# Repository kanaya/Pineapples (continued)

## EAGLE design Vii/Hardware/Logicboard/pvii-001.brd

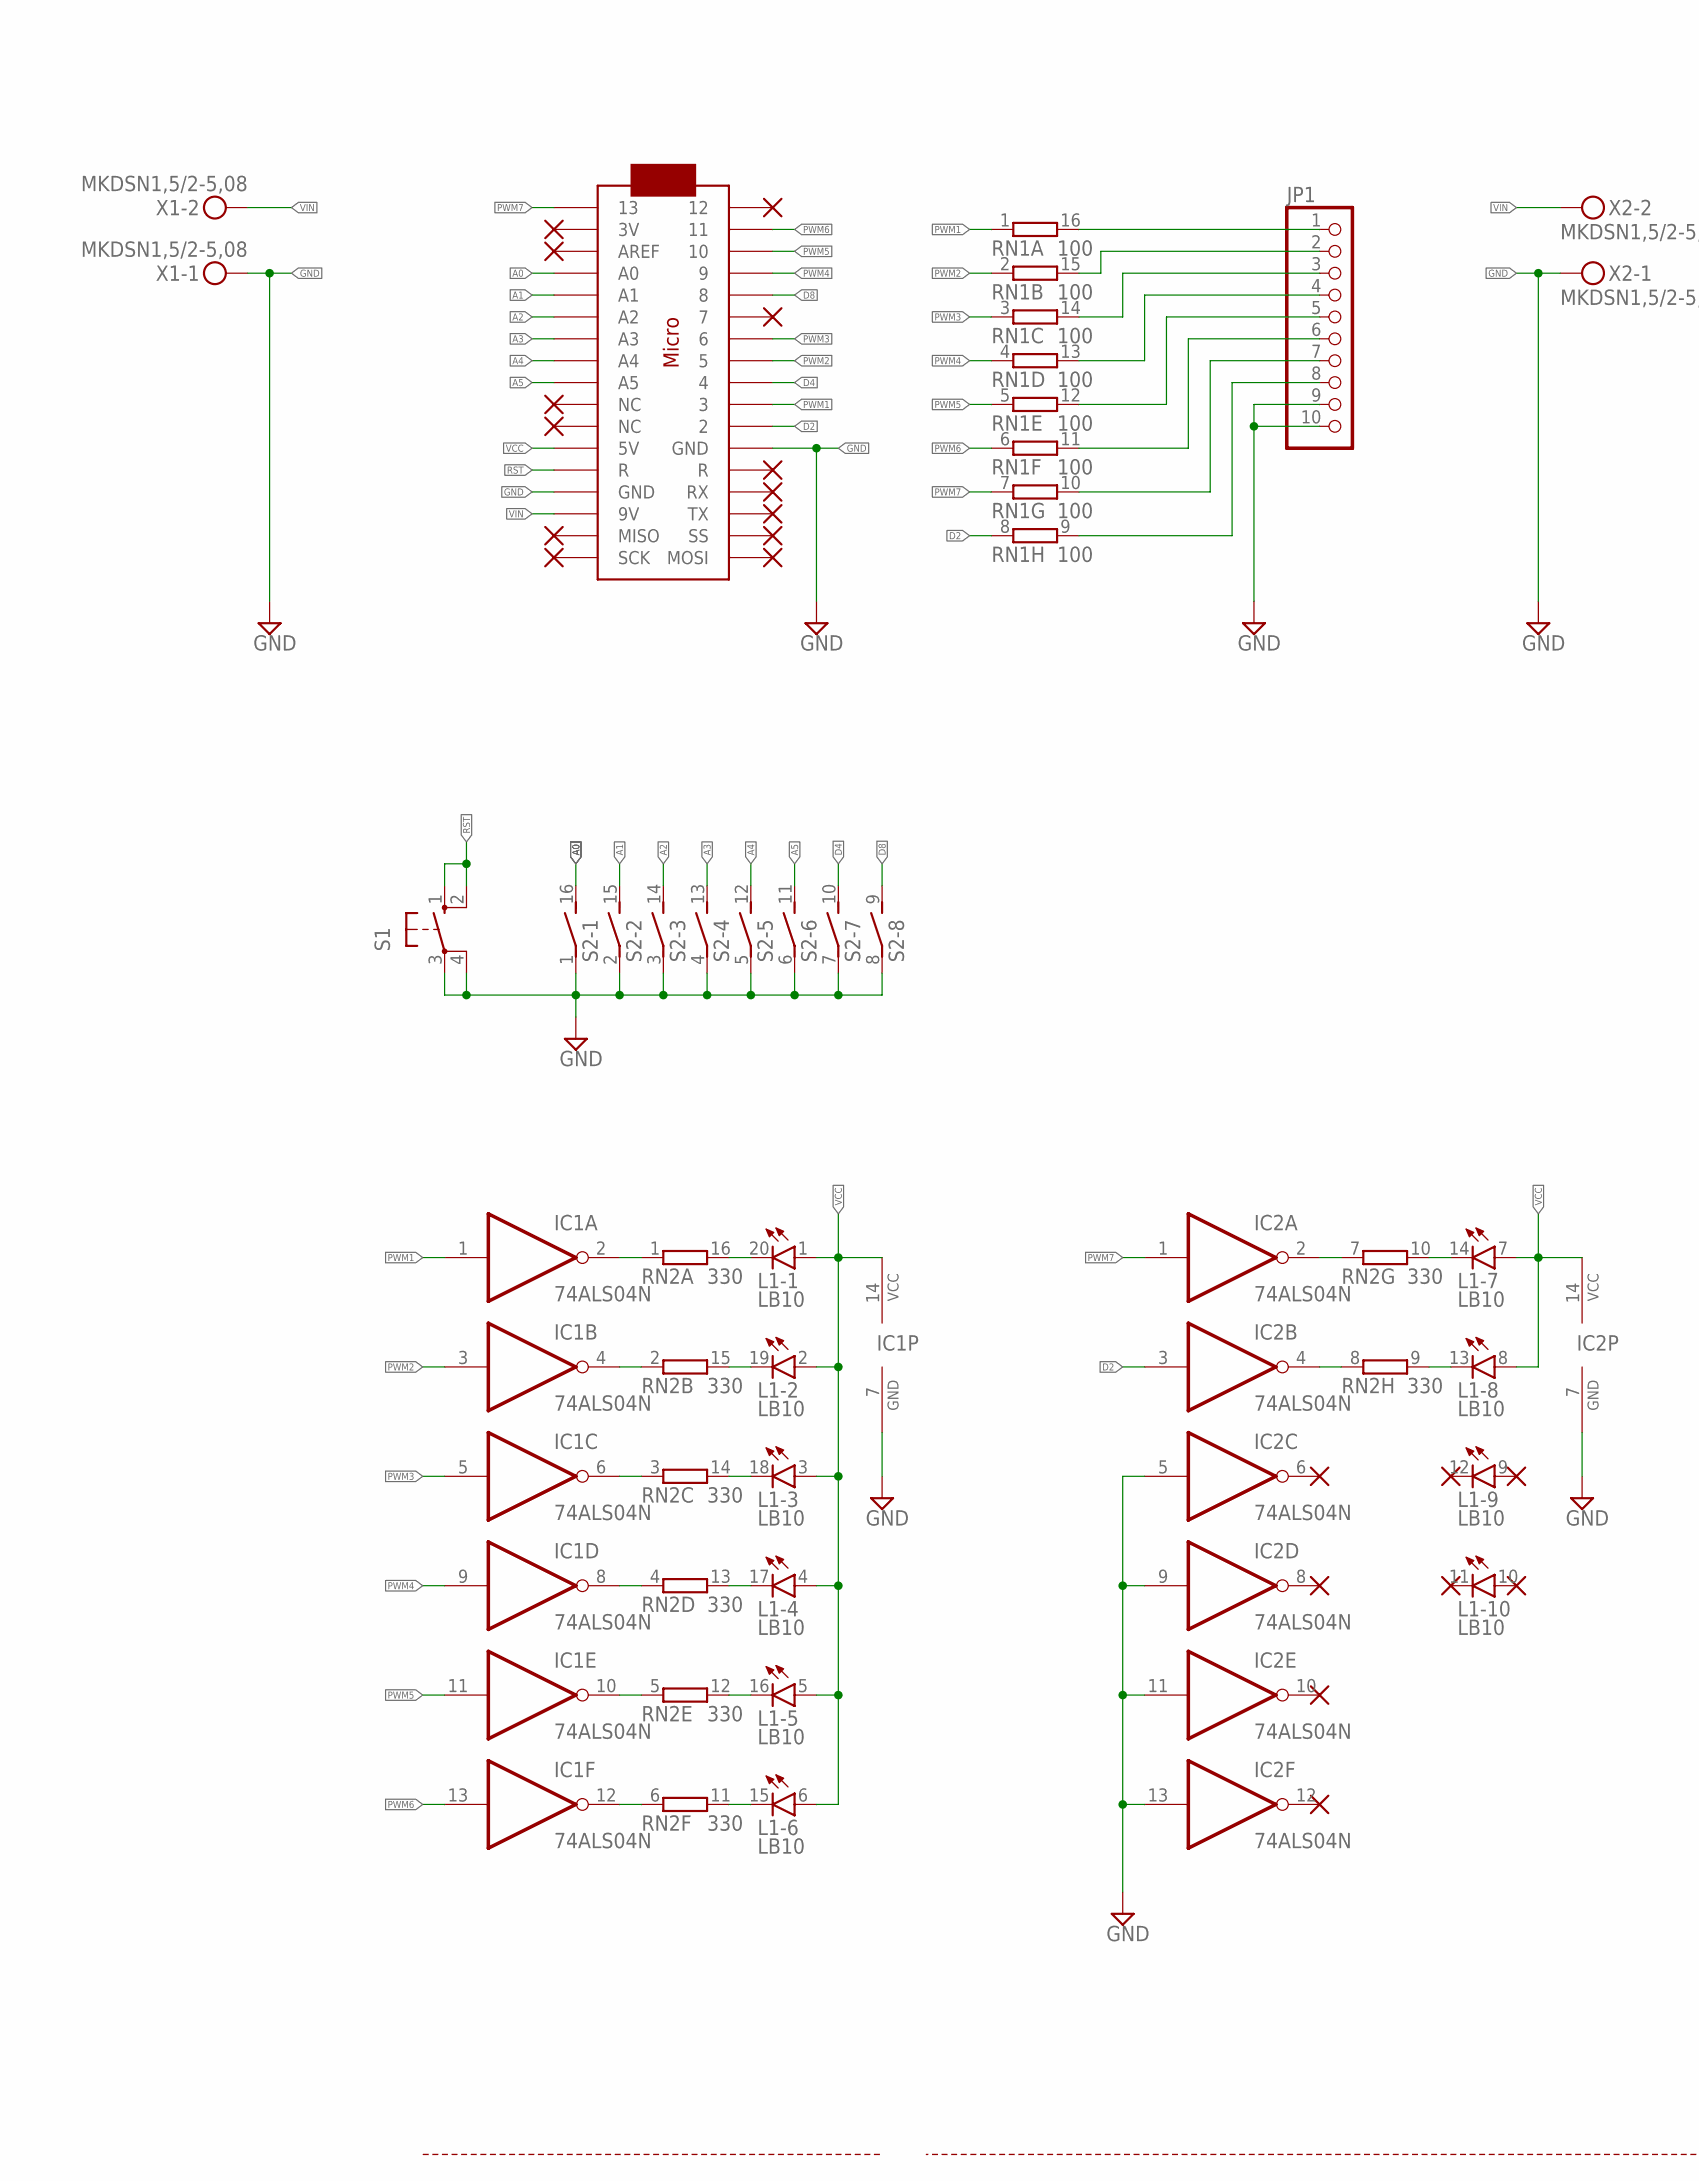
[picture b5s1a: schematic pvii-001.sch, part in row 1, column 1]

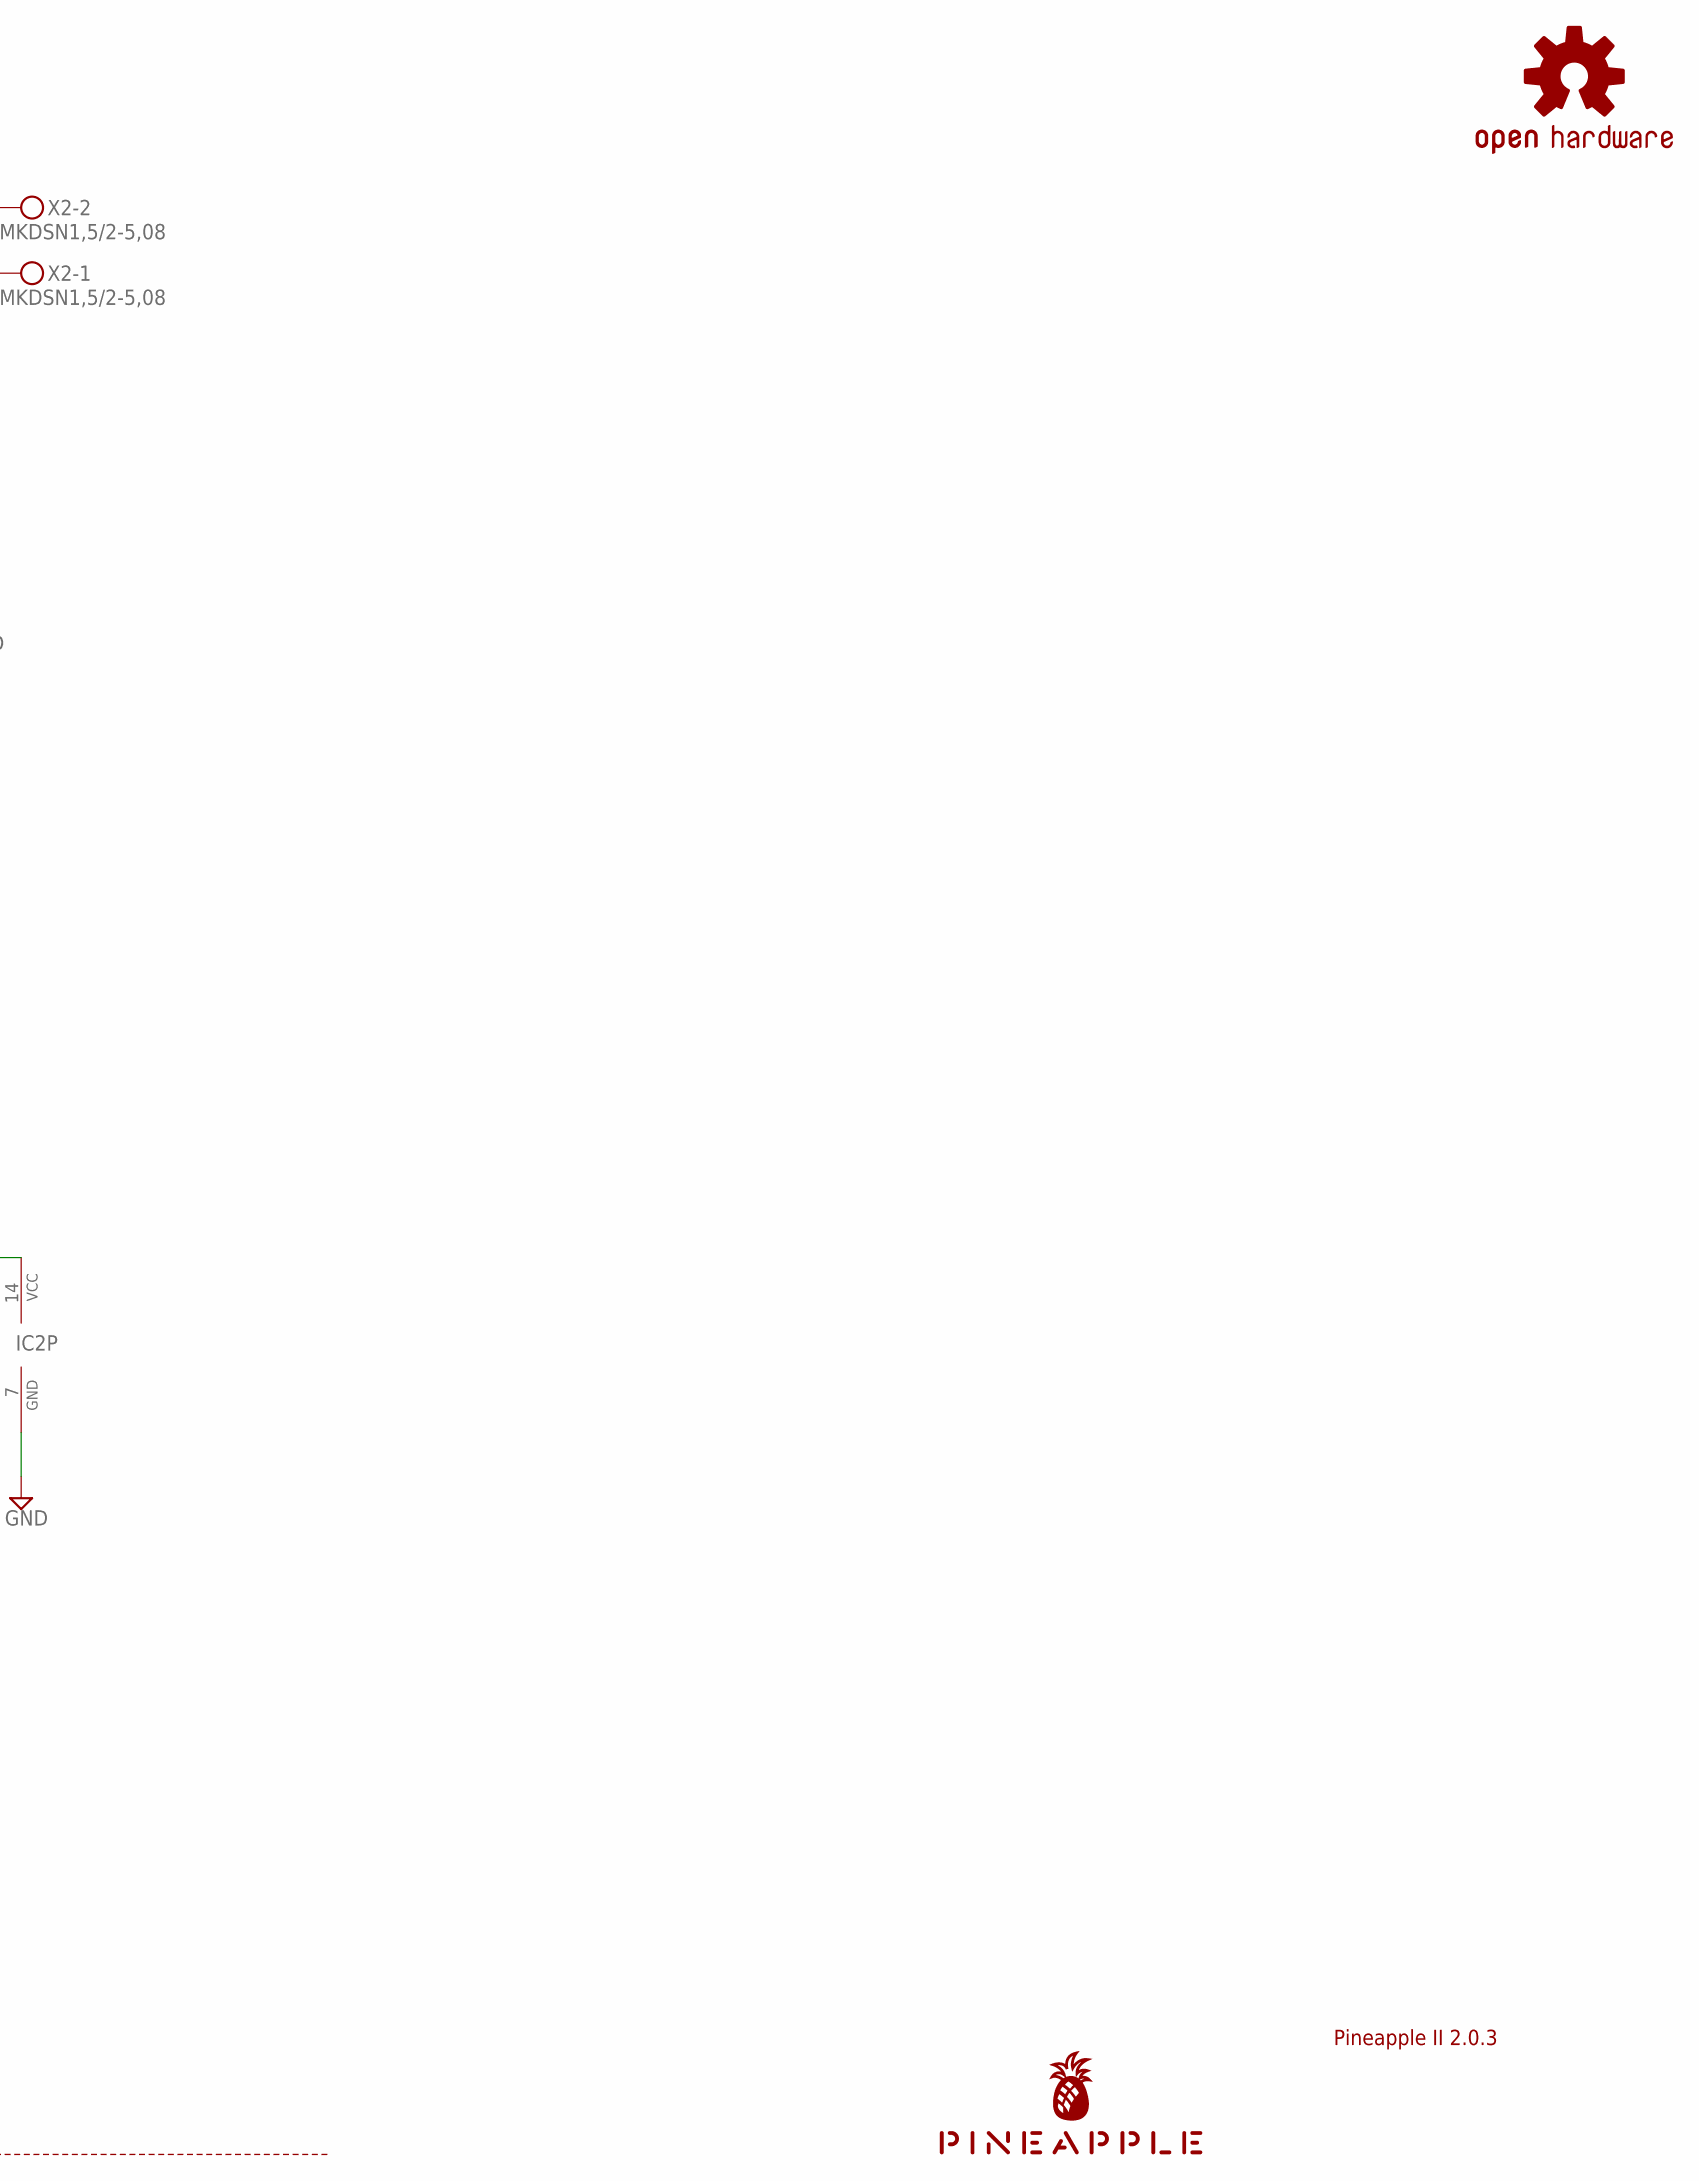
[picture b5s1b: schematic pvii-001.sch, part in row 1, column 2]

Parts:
IC1, IC2: 74ALS04N; DIL14
JP1: PINHD-1X10; 1X10
L1: LB10
LOGO1: OSHW-LOGOS-COPPER; OSHW-LOGO-S_COPPER
MC1: ARDUINOMICRO
RN1: 100; DIL16
RN2: 330; DIL16
S1: 10-XX; B3F-10XX
S2: DIP08S
U$1: PINEAPPLE450_SILK
X1, X2: MKDSN1,5/2-5,08

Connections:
A0: MC1.P$31 (A0), S2.16 (2)
A1: MC1.P$30 (A1), S2.15 (2)
A2: MC1.P$29 (A2), S2.14 (2)
A3: MC1.P$28 (A3), S2.13 (2)
A4: MC1.P$27 (A4), S2.12 (2)
A5: MC1.P$26 (A5), S2.11 (2)
D2: IC2.3 (I), MC1.P$11 (2), RN1.8 (1)
D4: MC1.P$9 (4), S2.10 (2)
D8: MC1.P$5 (8), S2.9 (2)
GND: IC1.7 (GND), IC2.5 (I), IC2.7 (GND), IC2.9 (I), IC2.11 (I), IC2.13 (I), JP1.9, JP1.10, MC1.P$12 (GND), MC1.P$21 (GND), S1.3, S1.4 (P1), S2.1, S2.2 (1), S2.3 (1), S2.4 (1), S2.5 (1), S2.6 (1), S2.7 (1), S2.8 (1), X1.1, X2.1
LED1: IC1.2 (O), RN2.1
LED1K: L1.20 (C), RN2.16 (2)
LED2: IC1.4 (O), RN2.2 (1)
LED2K: L1.19 (C), RN2.15 (2)
LED3: IC1.6 (O), RN2.3 (1)
LED3K: L1.18 (C), RN2.14 (2)
LED4: IC1.8 (O), RN2.4 (1)
LED4K: L1.17 (C), RN2.13 (2)
LED5: IC1.10 (O), RN2.5 (1)
LED5K: L1.16 (C), RN2.12 (2)
LED6: IC1.12 (O), RN2.6 (1)
LED6K: L1.15 (C), RN2.11 (2)
LED7: IC2.2 (O), RN2.7 (1)
LED7K: L1.14 (C), RN2.10 (2)
LED8: IC2.4 (O), RN2.8 (1)
LED8K: L1.13 (C), RN2.9 (2)
OUT1: JP1.1, RN1.16 (2)
OUT2: JP1.2, RN1.15 (2)
OUT3: JP1.3, RN1.14 (2)
OUT4: JP1.4, RN1.13 (2)
OUT5: JP1.5, RN1.12 (2)
OUT6: JP1.6, RN1.11 (2)
OUT7: JP1.7, RN1.10 (2)
OUT8: JP1.8, RN1.9 (2)
PWM1: IC1.1 (I), MC1.P$10 (3), RN1.1
PWM2: IC1.3 (I), MC1.P$8 (5), RN1.2 (1)
PWM3: IC1.5 (I), MC1.P$7 (6), RN1.3 (1)
PWM4: IC1.9 (I), MC1.P$4 (9), RN1.4 (1)
PWM5: IC1.11 (I), MC1.P$3 (10), RN1.5 (1)
PWM6: IC1.13 (I), MC1.P$2 (11), RN1.6 (1)
PWM7: IC2.1 (I), MC1.P$34 (13), RN1.7 (1)
RST: MC1.P$13 (R), S1.1 (S), S1.2 (S1)
VCC: IC1.14 (VCC), IC2.14 (VCC), L1.1 (A), L1.2 (A), L1.3 (A), L1.4 (A), L1.5 (A), L1.6 (A), L1.7 (A), L1.8 (A), MC1.P$23 (5V)
VIN: MC1.P$20 (9V), X1.2, X2.2

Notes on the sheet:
Pineapple II 2.0.3

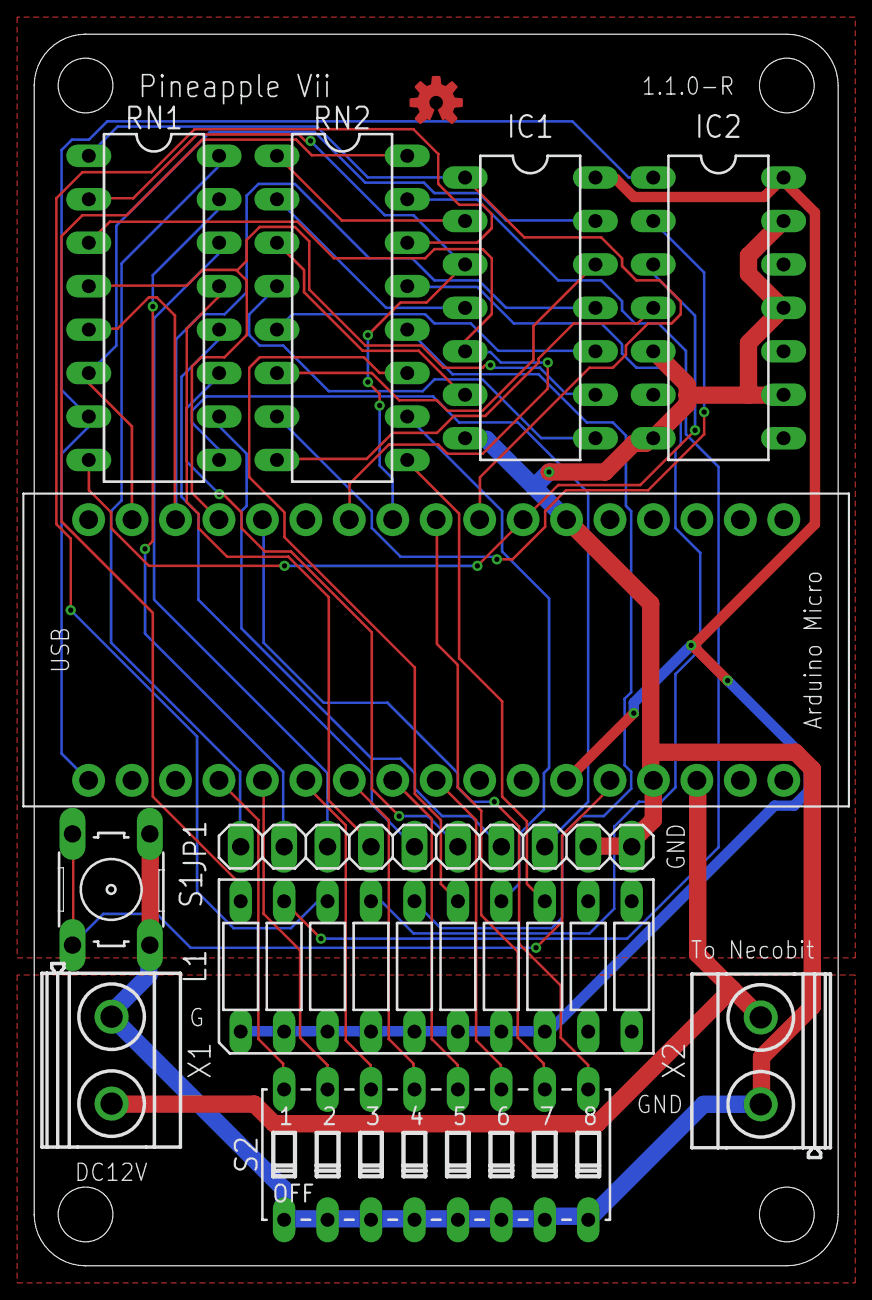
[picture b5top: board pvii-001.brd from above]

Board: 2 copper layers, 47.0 x 72.0 mm, 13 parts (1 on the bottom side), 44 nets.

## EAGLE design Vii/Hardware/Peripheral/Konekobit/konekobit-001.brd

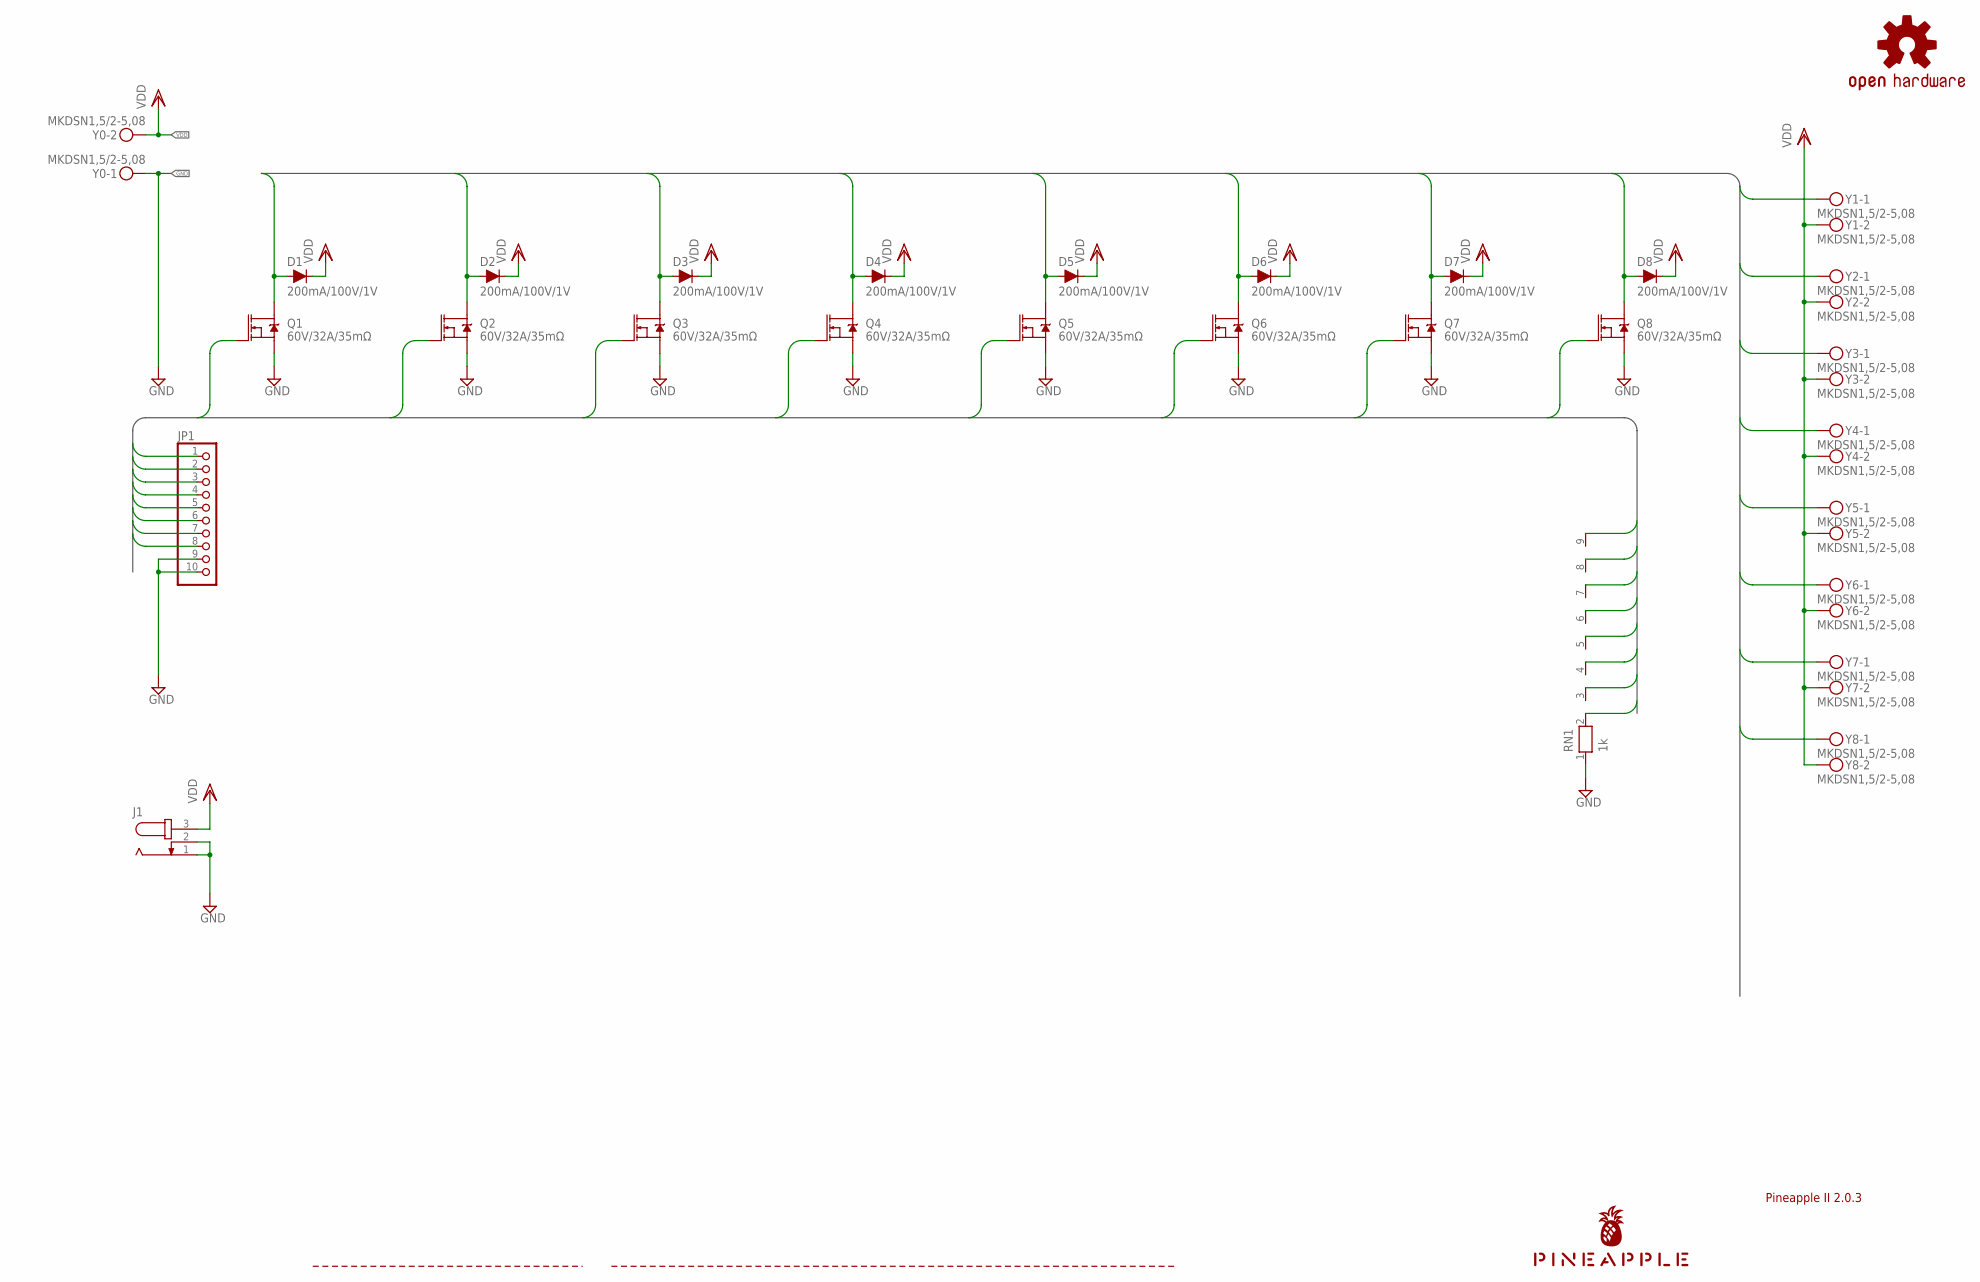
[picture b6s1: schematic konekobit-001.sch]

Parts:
D1, D2, D3, D4, D5, D6, D7, D8: 200mA/100V/1V; DIODE-1N4148
J1: JACK-PLUG0; SPC4077
JP1: PINHD-1X10; 1X10
LOGO1: OSHW-LOGOS-COPPER; OSHW-LOGO-S_COPPER
Q1, Q2, Q3, Q4, Q5, Q6, Q7, Q8: 60V/32A/35mΩ; TO220V
RN1: 1k; RN-9
U$1: PINEAPPLE450_SILK
Y0, Y1, Y2, Y3, Y4, Y5, Y6, Y7, Y8: MKDSN1,5/2-5,08

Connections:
DRAIN1: D1.A, Q1.2 (D), Y1.1
DRAIN2: D2.A, Q2.2 (D), Y2.1
DRAIN3: D3.A, Q3.2 (D), Y3.1
DRAIN4: D4.A, Q4.2 (D), Y4.1
DRAIN5: D5.A, Q5.2 (D), Y5.1
DRAIN6: D6.A, Q6.2 (D), Y6.1
DRAIN7: D7.A, Q7.2 (D), Y7.1
DRAIN8: D8.A, Q8.2 (D), Y8.1
GND: J1.1, J1.2, JP1.9, JP1.10, Q1.3 (S), Q2.3 (S), Q3.3 (S), Q4.3 (S), Q5.3 (S), Q6.3 (S), Q7.3 (S), Q8.3 (S), RN1.1, Y0.1
PWM1: JP1.1, Q1.1 (G), RN1.2
PWM2: JP1.2, Q2.1 (G), RN1.3
PWM3: JP1.3, Q3.1 (G), RN1.4
PWM4: JP1.4, Q4.1 (G), RN1.5
PWM5: JP1.5, Q5.1 (G), RN1.6
PWM6: JP1.6, Q6.1 (G), RN1.7
PWM7: JP1.7, Q7.1 (G), RN1.8
PWM8: JP1.8, Q8.1 (G), RN1.9
VDD: D1.C, D2.C, D3.C, D4.C, D5.C, D6.C, D7.C, D8.C, J1.3, Y0.2, Y1.2, Y2.2, Y3.2, Y4.2, Y5.2, Y6.2, Y7.2, Y8.2

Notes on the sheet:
Pineapple II 2.0.3

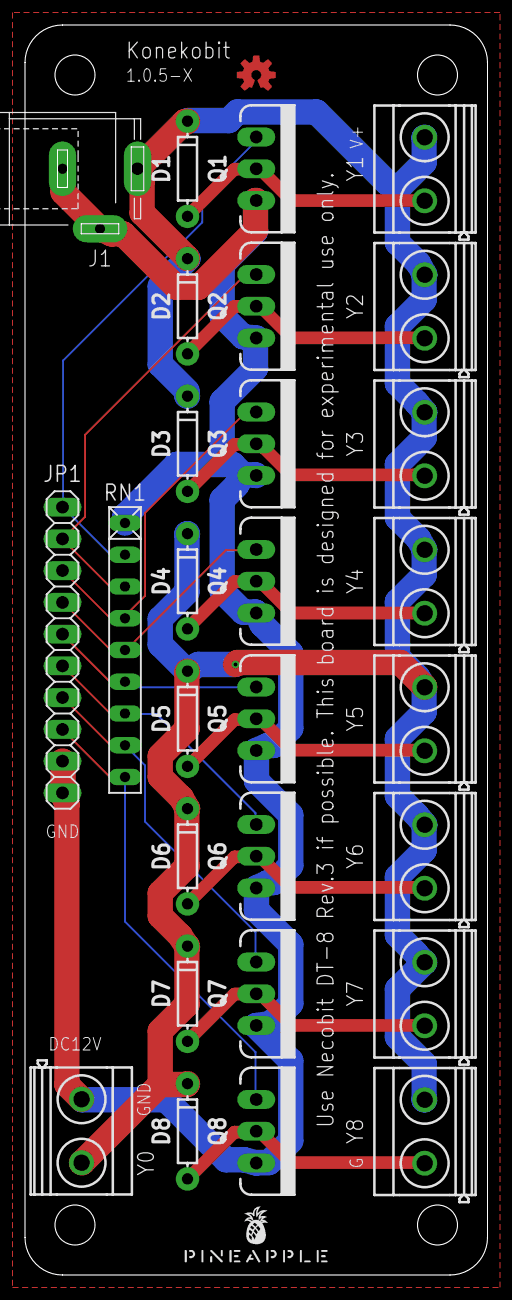
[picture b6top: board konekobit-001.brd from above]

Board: 2 copper layers, 37.0 x 100.0 mm, 30 parts (0 on the bottom side), 18 nets.

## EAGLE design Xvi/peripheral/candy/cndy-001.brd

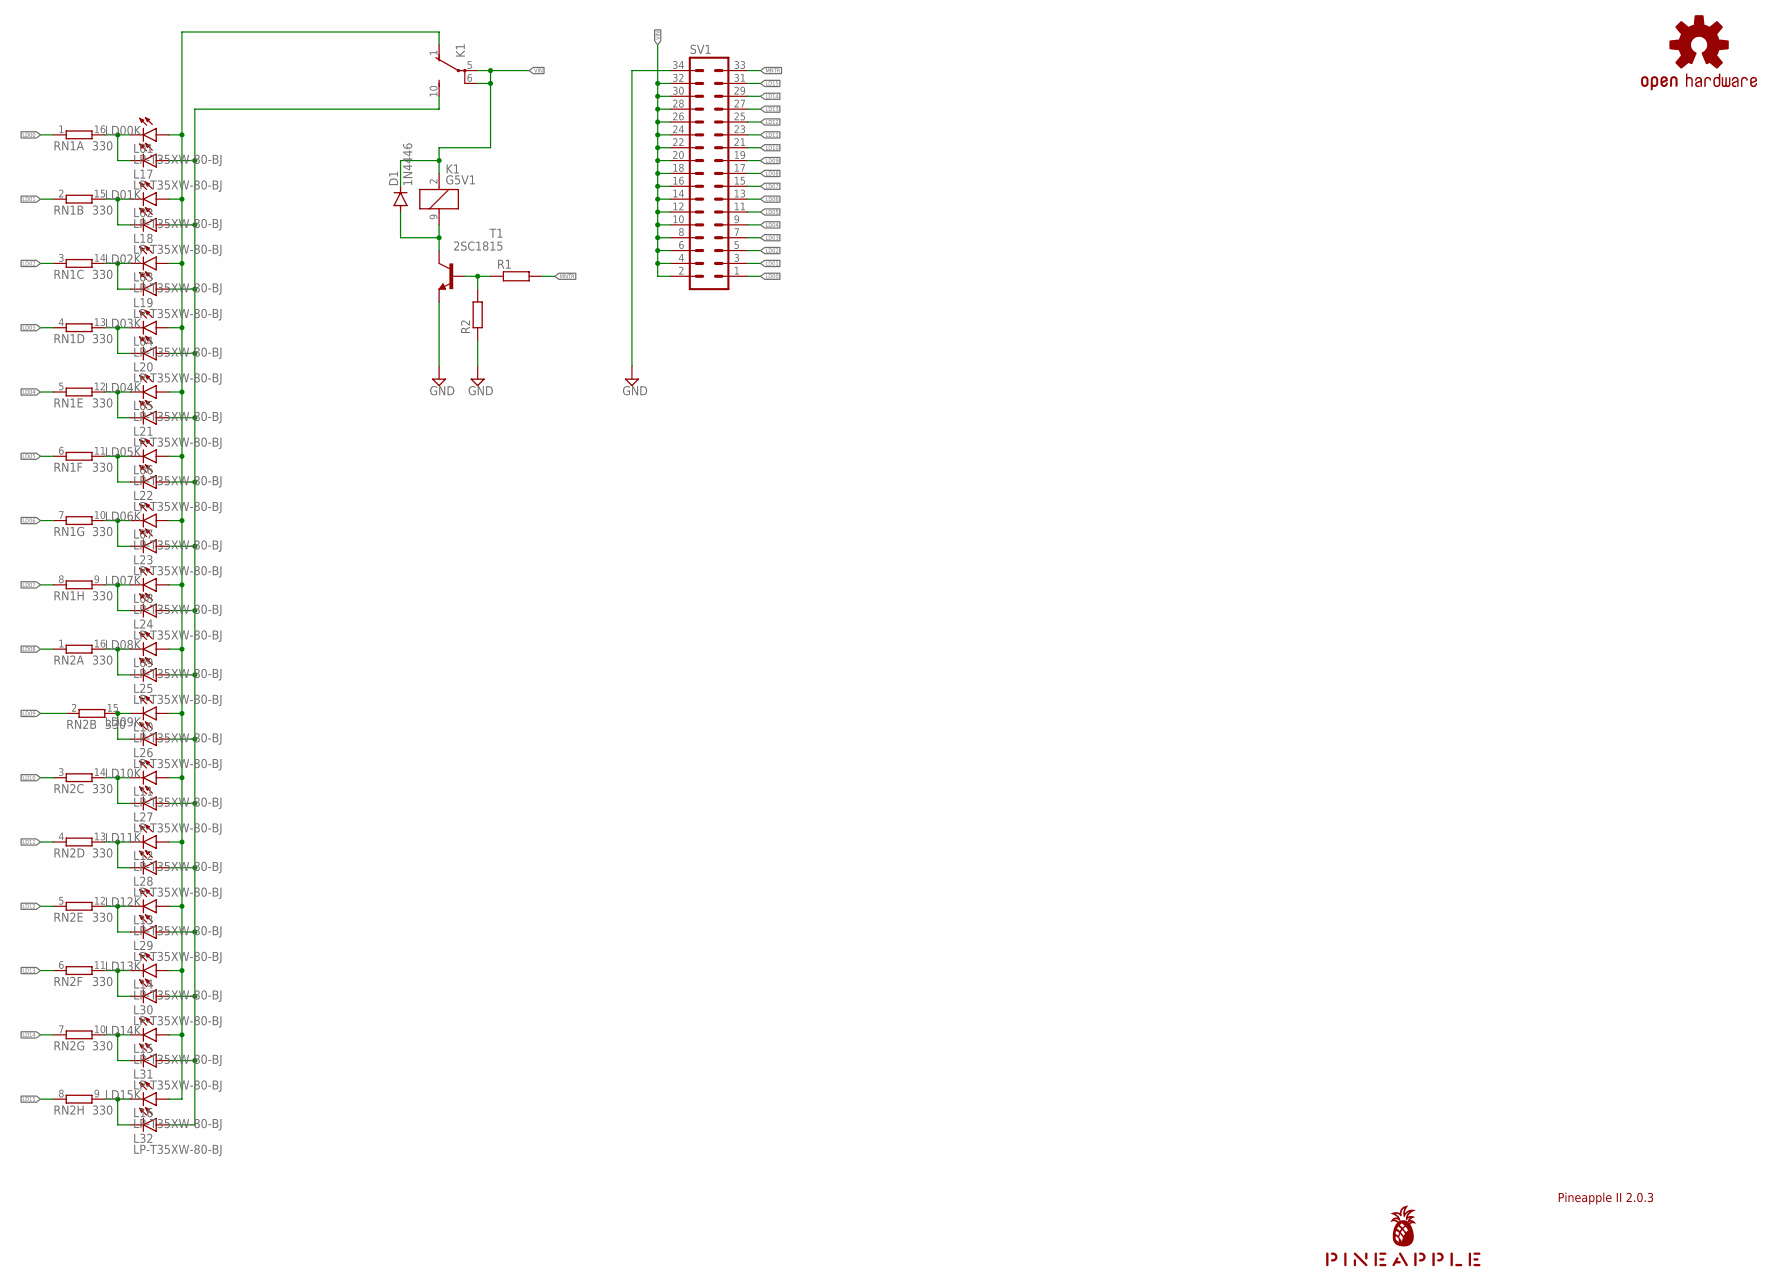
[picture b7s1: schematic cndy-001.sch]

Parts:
D1: 1N4446; DO35-10
K1: G5V1
L01, L02, L03, L04, L05, L06, L07, L08, L09, L10, L11, L12, L13, L14, L15, L16, L17, L18, L19, L20, L21, L22, L23, L24, L25, L26, L27, L28, L29, L30, L31, L32: LP-T35XW-80-BJ; KA-3528ASYC
LOGO1: OSHW-LOGOS-COPPER; OSHW-LOGO-S_COPPER
R1, R2: R-EU_0204/5; 0204/5
RN1, RN2: 330; DIL16
SV1: ML34L
T1: 2SC1815; TO92-ECB
U$1: PINEAPPLE450_SILK

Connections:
GND: R2.1, SV1.34, T1.E
LD00: RN1.1, SV1.1
LD00K: L01.C, L17.C, RN1.16 (2)
LD01: RN1.2 (1), SV1.3
LD01K: L02.C, L18.C, RN1.15 (2)
LD02: RN1.3 (1), SV1.5
LD02K: L03.C, L19.C, RN1.14 (2)
LD03: RN1.4 (1), SV1.7
LD03K: L04.C, L20.C, RN1.13 (2)
LD04: RN1.5 (1), SV1.9
LD04K: L05.C, L21.C, RN1.12 (2)
LD05: RN1.6 (1), SV1.11
LD05K: L06.C, L22.C, RN1.11 (2)
LD06: RN1.7 (1), SV1.13
LD06K: L07.C, L23.C, RN1.10 (2)
LD07: RN1.8 (1), SV1.15
LD07K: L08.C, L24.C, RN1.9 (2)
LD08: RN2.1, SV1.17
LD08K: L09.C, L25.C, RN2.16 (2)
LD09: RN2.2 (1), SV1.19
LD09K: L10.C, L26.C, RN2.15 (2)
LD10: RN2.3 (1), SV1.21
LD10K: L11.C, L27.C, RN2.14 (2)
LD11: RN2.4 (1), SV1.23
LD11K: L12.C, L28.C, RN2.13 (2)
LD12: RN2.5 (1), SV1.25
LD12K: L13.C, L29.C, RN2.12 (2)
LD13: RN2.6 (1), SV1.27
LD13K: L14.C, L30.C, RN2.11 (2)
LD14: RN2.7 (1), SV1.29
LD14K: L15.C, L31.C, RN2.10 (2)
LD15: RN2.8 (1), SV1.31
LD15K: L16.C, L32.C, RN2.9 (2)
MNTR: R1.2, SV1.33
unnamed: D1.A, K1.9 (2), T1.C
unnamed: R1.1, R2.2, T1.B
VIN: D1.C, K1.2 (1), K1.5, K1.6, SV1.2, SV1.4, SV1.6, SV1.8, SV1.10, SV1.12, SV1.14, SV1.16, SV1.18, SV1.20, SV1.22, SV1.24, SV1.26, SV1.28, SV1.30, SV1.32
VINA: K1.1 (O), L01.A, L02.A, L03.A, L04.A, L05.A, L06.A, L07.A, L08.A, L09.A, L10.A, L11.A, L12.A, L13.A, L14.A, L15.A, L16.A
VINB: K1.10 (S), L17.A, L18.A, L19.A, L20.A, L21.A, L22.A, L23.A, L24.A, L25.A, L26.A, L27.A, L28.A, L29.A, L30.A, L31.A, L32.A

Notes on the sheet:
Pineapple II 2.0.3

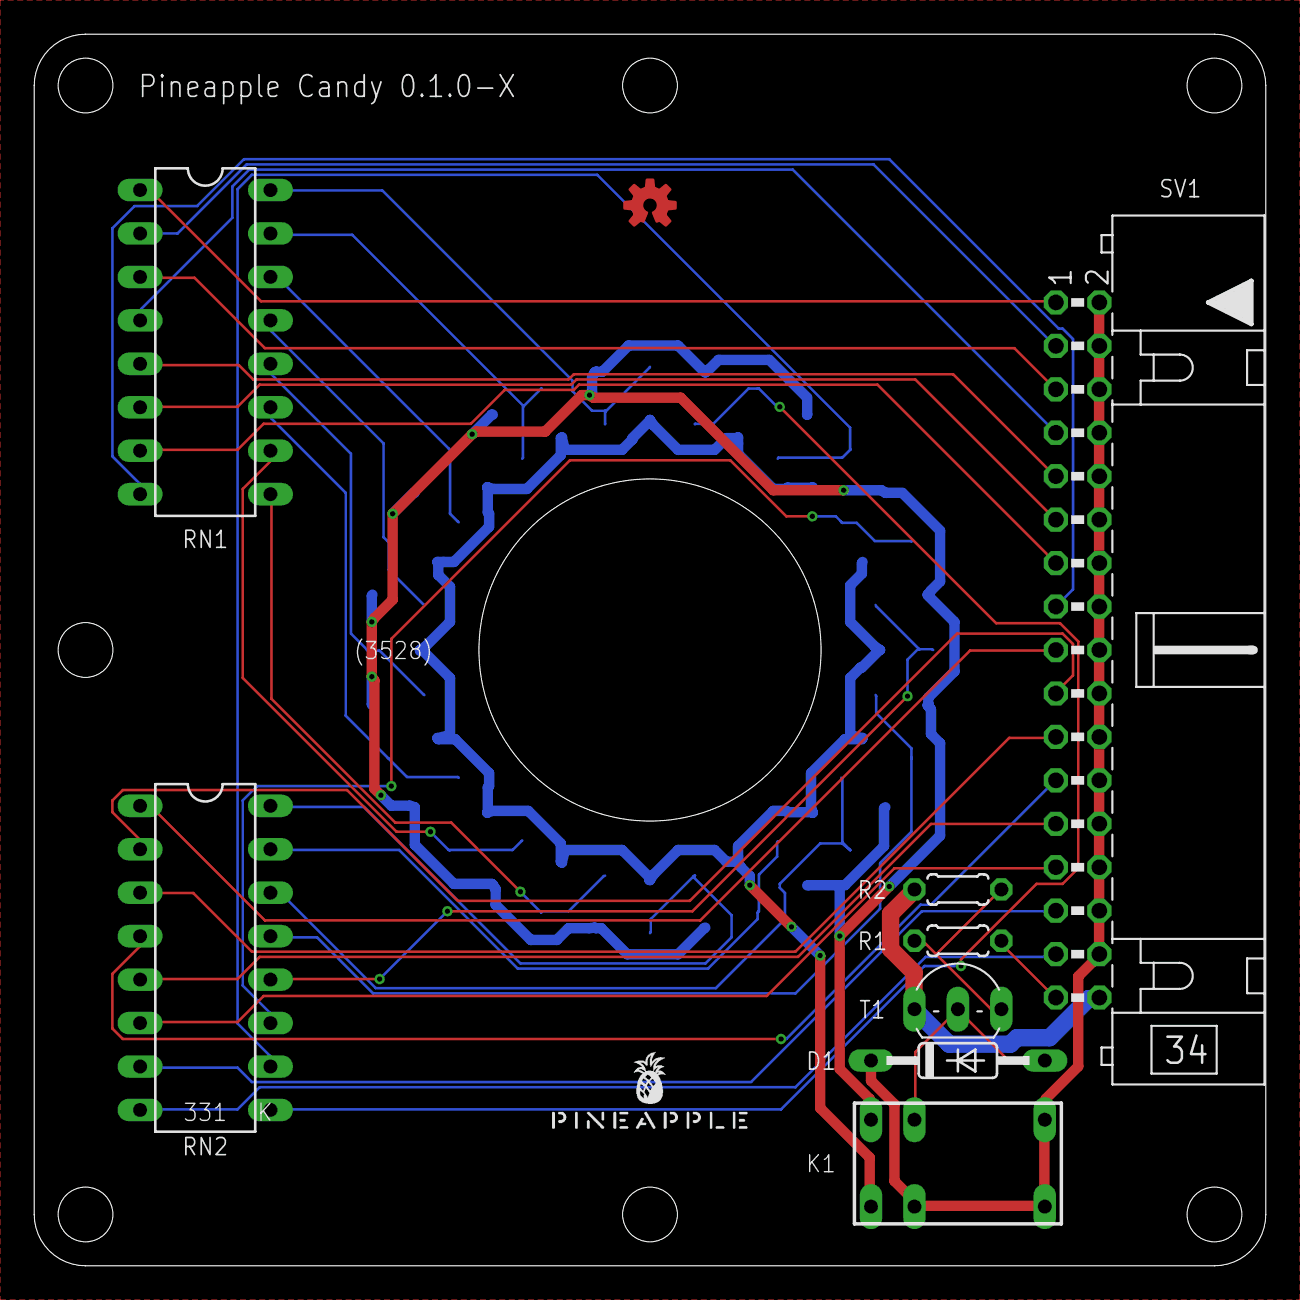
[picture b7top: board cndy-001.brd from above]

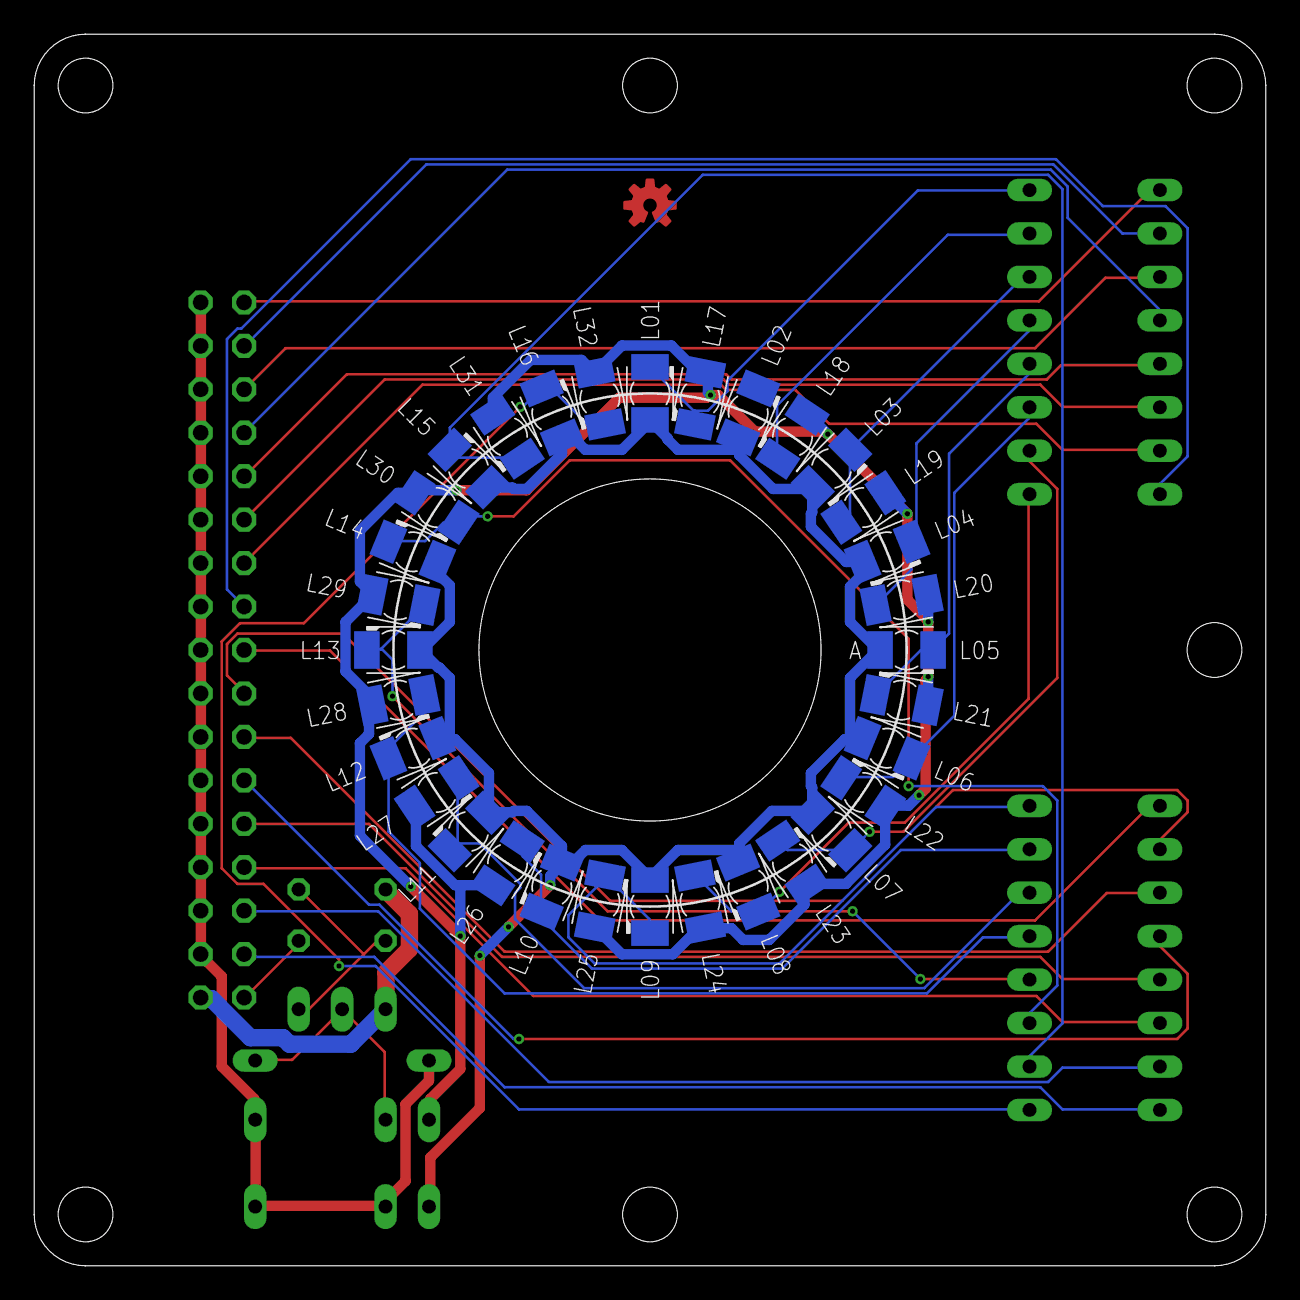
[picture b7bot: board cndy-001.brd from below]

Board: 2 copper layers, 72.0 x 72.0 mm, 42 parts (32 on the bottom side), 39 nets.
